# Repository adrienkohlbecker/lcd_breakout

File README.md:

# LCD breakout

## Board

## Schematic

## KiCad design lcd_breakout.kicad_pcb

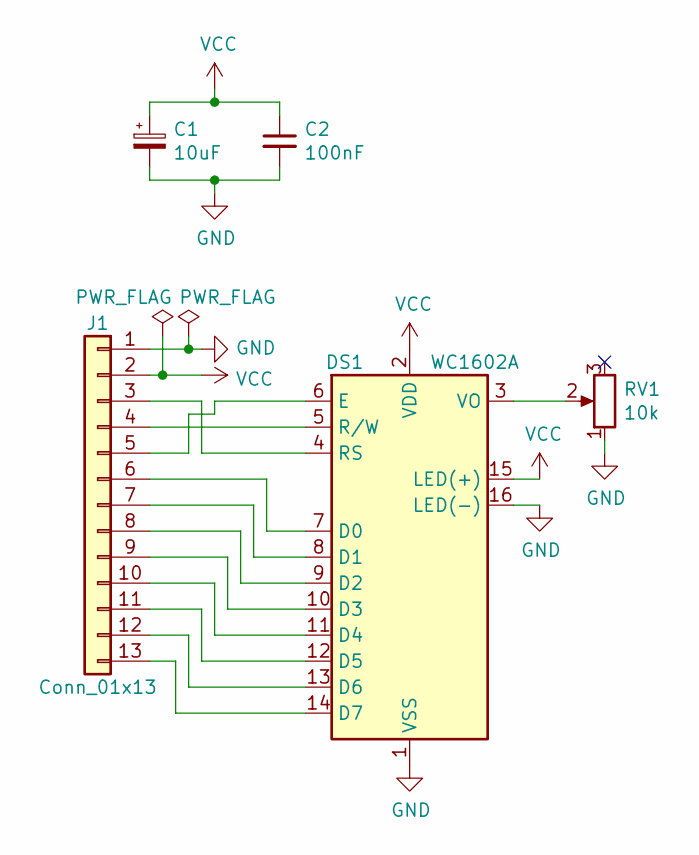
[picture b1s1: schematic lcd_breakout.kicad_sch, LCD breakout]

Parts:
C1: 10uF; CP_Radial_D4.0mm_P2.00mm
C2: 100nF; C_Disc_D3.4mm_W2.1mm_P2.50mm
DS1: WC1602A
J1: Conn_01x13; PinSocket_1x13_P2.54mm_Vertical
RV1: 10k; 3352W1502LF

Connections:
GND: C1.2, C2.2, DS1.1 (VSS), DS1.16 (LED(-)), J1.1, RV1.1
unnamed: DS1.3 (VO), RV1.2
unnamed: DS1.4 (RS), J1.3
unnamed: DS1.5 (R/W), J1.4
unnamed: DS1.6 (E), J1.5
unnamed: DS1.7 (D0), J1.6
unnamed: DS1.8 (D1), J1.7
unnamed: DS1.9 (D2), J1.8
unnamed: DS1.10 (D3), J1.9
unnamed: DS1.11 (D4), J1.10
unnamed: DS1.12 (D5), J1.11
unnamed: DS1.13 (D6), J1.12
unnamed: DS1.14 (D7), J1.13
VCC: C1.1, C2.1, DS1.2 (VDD), DS1.15 (LED(+)), J1.2

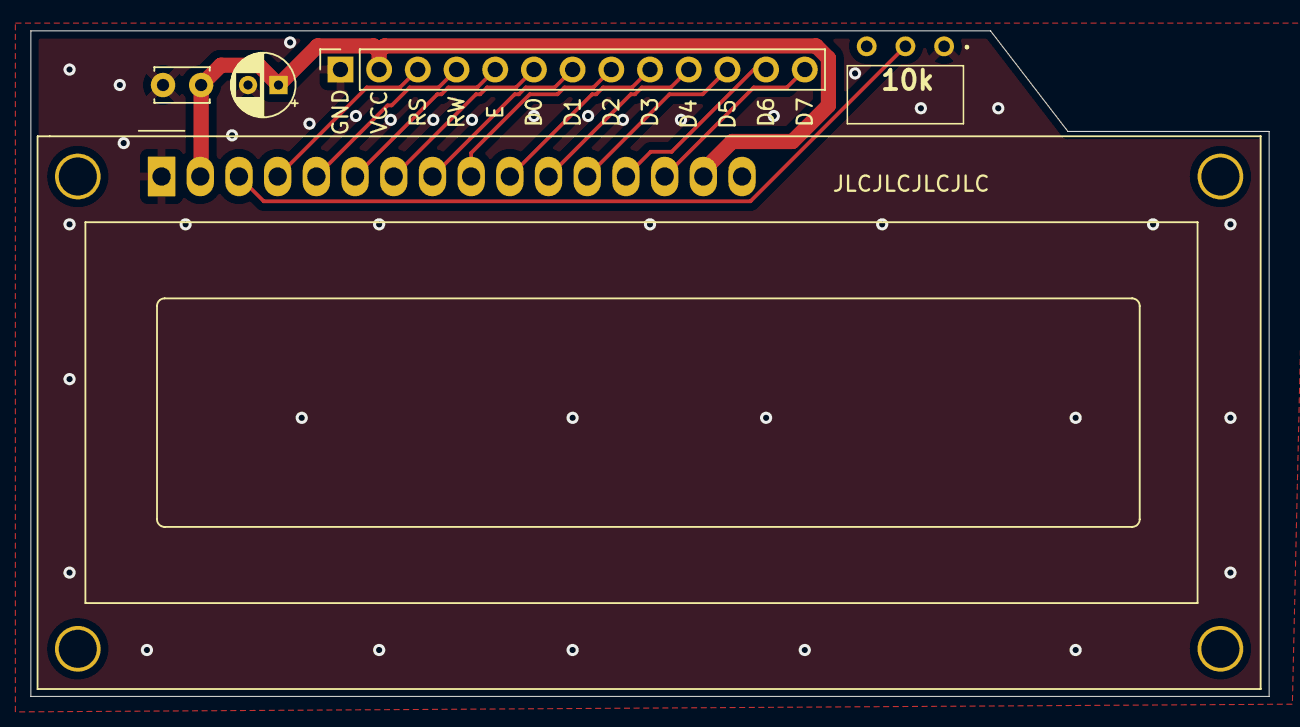
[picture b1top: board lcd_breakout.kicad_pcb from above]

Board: 2 copper layers, 81.3 x 43.7 mm, 5 parts (0 on the bottom side), 14 nets.

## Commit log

2021-10-29 Add LCD
2021-12-13 Update LCD
2021-12-19 Remove ignored files
2023-06-07 Update for KiCad 6
